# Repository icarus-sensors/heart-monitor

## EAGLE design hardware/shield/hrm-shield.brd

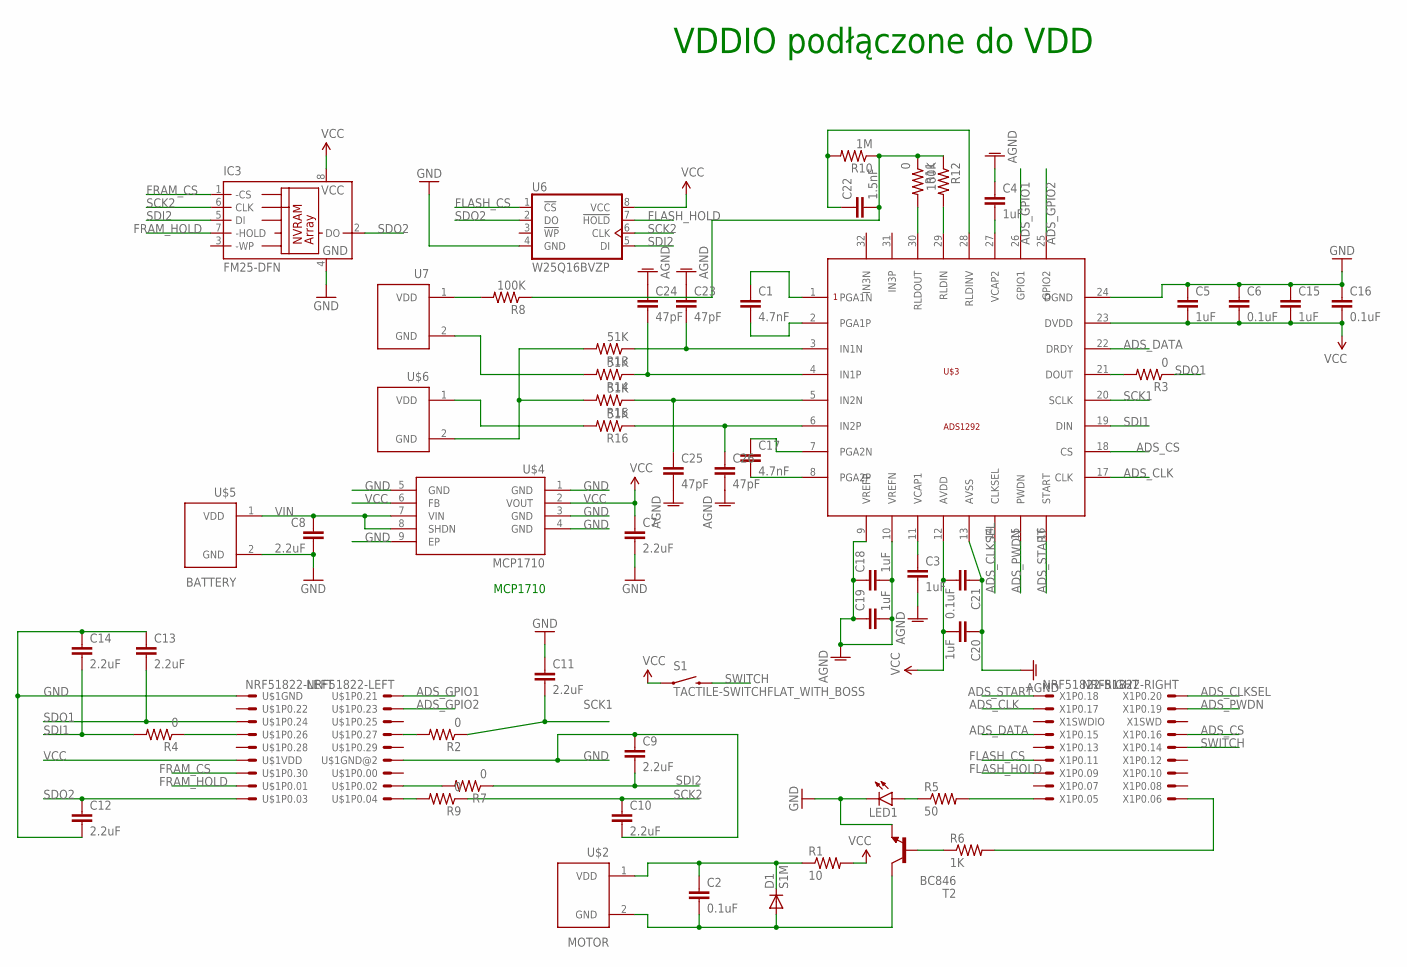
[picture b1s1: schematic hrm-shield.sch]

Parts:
C1, C17: 4.7nF; 0603-CAP
C2, C6, C16, C21: 0.1uF; 0603-CAP
C3, C4, C5, C15, C18, C19, C20: 1uF; 0603-CAP
C7, C8, C9, C10, C11, C12, C13, C14: 2.2uF; 0603-CAP
C22: 1.5nF; 0603-CAP
C23, C24, C25, C26: 47pF; 0603-CAP
D1: S1M; SMA
IC3: FM25-DFN; DFN-8
LED1: LED0603; LED-0603
R1: 10; 0603-RES
R2, R3, R4, R7, R9, R11: 0; 0603-RES
R5: 50; 0603-RES
R6: 1K; 0603-RES
R8, R12: 100K; 0603-RES
R10: 1M; 0603-RES
R13, R14, R15, R16: 51K; 0603-RES
S1: TACTILE-SWITCHFLAT_WITH_BOSS; TACTILE-SWITCH-SMD
T2: BC846; SOT23
U6: W25Q16BVZP; WSON8
U7: EM406-2PINFLAT; EM406-2PIN
U$1: NRF51822-LEFT
U$2: MOTOR; EM406-2PIN
U$3: ADS1292; QFN-32-4X4
U$4: MCP1710
U$5: BATTERY; EM406-2PIN
U$6: EM406-2PINFLAT; EM406-2PIN
X1: NRF51822-RIGHT

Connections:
ADS_CLK: U$3.17 (CLK), X1.3
ADS_CLKSEL: U$3.14 (CLKSEL), X1.2
ADS_CS: U$3.18 (CS), X1.8
ADS_DATA: U$3.22 (DRDY), X1.7
ADS_GPIO1: U$1.2, U$3.26 (GPIO1)
ADS_GPIO2: U$1.4, U$3.25 (GPIO2)
ADS_PWDN: U$3.15 (PWDN), X1.4
ADS_START: U$3.16 (START), X1.1
AGND: C3.2, C4.1, C18.1, C18.2, C19.1, C19.2, C20.1, C21.1, C23.1, C24.1, C25.2, C26.2, U$3.9 (VREFP), U$3.10 (VREFN), U$3.13 (AVSS)
FLASH_CS: U6.1 (!CS!), X1.11
FLASH_HOLD: U6.7 (!HOLD!), X1.13
FRAM_CS: IC3.1 (-CS), U$1.13
FRAM_HOLD: IC3.7 (-HOLD), U$1.15
GND: C5.1, C6.1, C7.2, C8.2, C9.1, C10.2, C11.1, C12.2, C13.1, C14.1, C15.1, C16.1, IC3.4 (GND), LED1.C, T2.2 (E), U6.4 (GND), U$1.1, U$1.12, U$3.24 (DGND), U$4.1 (GND), U$4.3 (GND), U$4.4 (GND), U$4.5 (GND), U$4.9 (EP), U$5.2 (GND)
unnamed: C4.2, U$3.27 (VCAP2)
unnamed: C2.1, D1.C, R1.1, U$2.1 (VDD)
unnamed: R4.1, U$1.7
unnamed: R2.2, U$1.8
unnamed: R7.2, U$1.16
unnamed: R5.2, X1.17
unnamed: C3.1, U$3.11 (VCAP1)
unnamed: R9.2, U$1.18
unnamed: C1.1, U$3.1 (PGA1N)
unnamed: C1.2, U$3.2 (PGA1P)
unnamed: R11.2, U$3.30 (RLDOUT)
unnamed: C17.2, U$3.8 (PGA2P)
unnamed: LED1.A, R5.1
unnamed: C2.2, D1.A, T2.3 (C), U$2.2 (GND)
unnamed: R6.2, X1.18
unnamed: R6.1, T2.1 (B)
unnamed: R3.2, U$3.21 (DOUT)
unnamed: C17.1, U$3.7 (PGA2N)
unnamed: R12.2, U$3.29 (RLDIN)
unnamed: C22.2, R8.1, R10.1, R11.1, R12.1
unnamed: C22.1, R10.2, U$3.28 (RLDINV)
unnamed: R8.2, U7.1 (VDD)
unnamed: C26.1, R16.1, U$3.6 (IN2P)
unnamed: C25.1, R15.1, U$3.5 (IN2N)
unnamed: C23.2, R13.1, U$3.3 (IN1N)
unnamed: C24.2, R14.1, U$3.4 (IN1P)
unnamed: R13.2, R15.2, U$6.2 (GND)
unnamed: R16.2, U$6.1 (VDD)
unnamed: R14.2, U7.2 (GND)
SCK1: C11.2, R2.1, U$3.20 (SCLK)
SCK2: C10.1, IC3.6 (CLK), R9.1, U6.6 (CLK)
SDI1: C14.2, R4.2, U$3.19 (DIN)
SDI2: C9.2, IC3.5 (DI), R7.1, U6.5 (DI)
SDO1: C13.2, R3.1, U$1.5
SDO2: C12.1, IC3.2 (DO), U6.2 (DO), U$1.17
SWITCH: S1.2, X1.10
VCC: C5.2, C6.2, C7.1, C15.2, C16.2, C20.2, C21.2, IC3.8 (VCC), R1.2, S1.1, U6.8 (VCC), U$1.11, U$3.12 (AVDD), U$3.23 (DVDD), U$4.2 (VOUT), U$4.6 (FB)
VIN: C8.1, U$4.7 (VIN), U$4.8 (SHDN), U$5.1 (VDD)

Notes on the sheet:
MCP1710
VDDIO podłączone do VDD

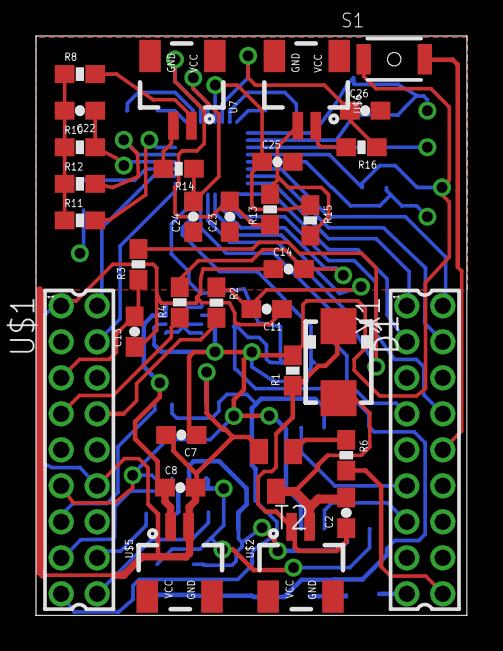
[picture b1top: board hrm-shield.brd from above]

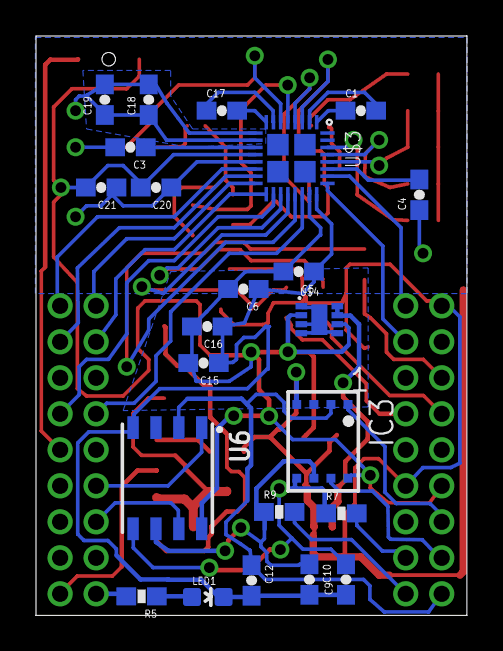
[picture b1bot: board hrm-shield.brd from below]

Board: 2 copper layers, 23.9 x 32.2 mm, 56 parts (23 on the bottom side), 52 nets.

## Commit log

2014-12-10 initial version / copy from 9DOF
2014-12-10 scheme with ada1292
2014-12-15 revA
2014-12-15 revA - fixes

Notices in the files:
parts and their libraries:
SparkFun-Resistors: Licensing: Creative Commons ShareAlike 4.0 International - https://creativecommons.org/licenses/by-sa/4.0
